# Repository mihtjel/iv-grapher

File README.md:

# iv-grapher
IV graphing electronics project. KiCAD design and Python (PyQT) based software.

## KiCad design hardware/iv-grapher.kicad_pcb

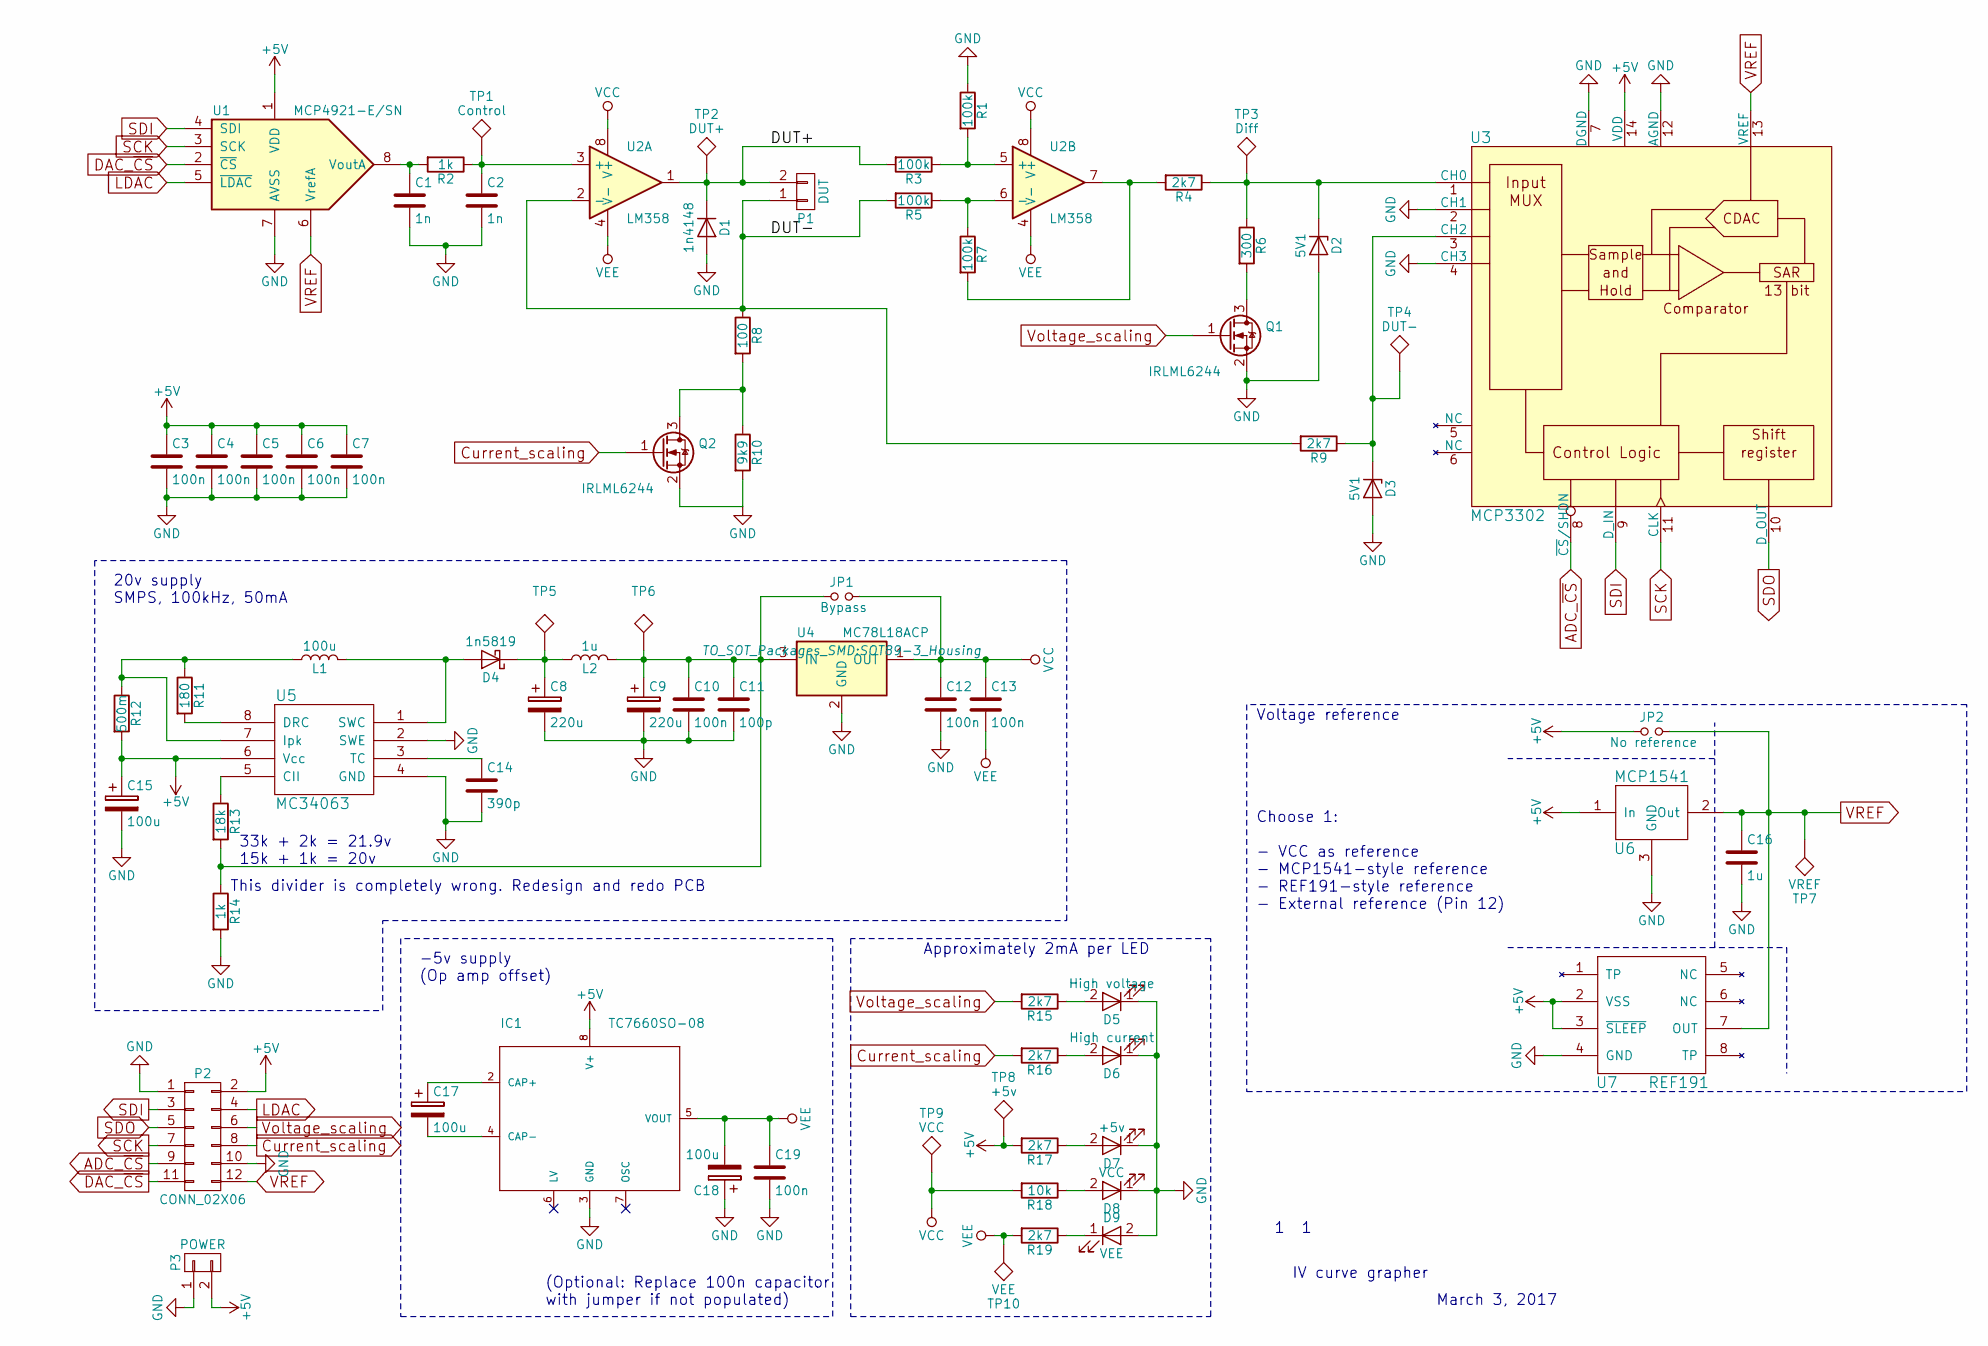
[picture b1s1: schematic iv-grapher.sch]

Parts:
C1, C2: 1n; C_0805
C3, C4, C5, C6, C7, C10, C12, C13, C19: 100n; C_0805
C8, C9: 220u; C_Radial_D8_L11.5_P3.5
C11: 100p; C_0805
C14: 390p; C_0805
C15, C17, C18: 100u; C_Radial_D6.3_L11.2_P2.5
C16: 1u; C_0805
D1: 1n4148; R_0805
D2, D3: 5V1; SOD-123
D4: 1n5819; SOD-123
D5: High voltage; R_0805
D6: High current; R_0805
D7: +5v; R_0805
D8: VCC; R_0805
D9: VEE; R_0805
IC1: TC7660SO-08; SOIC-8_3.9x4.9mm_Pitch1.27mm
JP1: Bypass; R_0805
JP2: No reference; R_0805
L1: 100u; Choke_SMD_6.3x6.3_H3
L2: 1u; R_0805
P1: DUT; DG306-5.0_2-pin
P2: CONN_02X06; IDC_Header_Straight_12pins
P3: POWER; Pin_Header_Straight_1x02
Q1, Q2: IRLML6244; SOT-23
R1, R3, R5, R7: 100k; R_0805
R2, R14: 1k; R_0805
R4, R9, R15, R16, R17, R19: 2k7; R_0805
R6: 300; R_0805
R8: 100; R_0805
R10: 9k9; R_0805
R11: 180; R_0805
R12: 500m; R_0805
R13: 18k; R_0805
R18: 10k; R_0805
TP1: Control; Measurement_Point_Round-SMD-Pad_Small
TP2: DUT+; Measurement_Point_Round-SMD-Pad_Small
TP3: Diff; Measurement_Point_Round-SMD-Pad_Small
TP4: DUT-; Measurement_Point_Round-SMD-Pad_Small
TP5: VCC pre filter; Measurement_Point_Round-SMD-Pad_Small
TP6: VCC post filter; Measurement_Point_Round-SMD-Pad_Small
TP7: VREF; Measurement_Point_Round-SMD-Pad_Small
TP8: +5v; Measurement_Point_Round-SMD-Pad_Small
TP9: VCC; Measurement_Point_Round-SMD-Pad_Small
TP10: VEE; Measurement_Point_Round-SMD-Pad_Small
U1: MCP4921-E/SN; SOIC-8_3.9x4.9mm_Pitch1.27mm
U2: LM358; SOIC-8_3.9x4.9mm_Pitch1.27mm
U3: MCP3302; SOIC-14_3.9x8.7mm_Pitch1.27mm
U4: MC78L18ACP; SOT89-3_Housing
U5: MC34063; SOIC-8_3.9x4.9mm_Pitch1.27mm
U6: MCP1541; SOT-23
U7: REF191; SOIC-8_3.9x4.9mm_Pitch1.27mm

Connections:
+5V: C3.1, C4.1, C5.1, C6.1, C7.1, C15.1, IC1.8 (V+), JP2.1, P2.2, P3.2, R12.2, R17.2, TP8.1, U1.1 (VDD), U3.14 (VDD), U5.6 (Vcc), U6.1 (In), U7.2 (VSS), U7.3 (~SLEEP)
/DUT+: D1.1 (K), P1.2, R3.2, TP2.1, U2.1
/DUT-: P1.1, R5.2, R8.1, R9.2, U2.2 (-)
ADC_~CS: P2.9, U3.8 (~CS~/SHDN)
Current_scaling: P2.8, Q2.1 (G), R16.2
DAC_~CS: P2.11, U1.2 (~CS~)
GND: C1.2, C2.2, C3.2, C4.2, C5.2, C6.2, C7.2, C8.2, C9.2, C10.2, C11.2, C12.2, C14.2, C15.2, C16.2, C18.1, C19.2, D1.2 (A), D2.2 (A), D3.2 (A), D5.1 (K), D6.1 (K), D7.1 (K), D8.1 (K), D9.2 (A), IC1.3 (GND), P2.1, P2.10, P3.1, Q1.2 (S), Q2.2 (S), R1.1, R10.2, R14.2, U1.7 (AVSS), U3.2 (CH1), U3.4 (CH3), U3.7 (DGND), U3.12 (AGND), U4.2 (GND), U5.2 (SWE), U5.4 (GND), U6.3 (GND), U7.4 (GND)
LDAC: P2.4, U1.5 (~LDAC~)
unnamed: C1.1, R2.2, U1.8 (VoutA)
unnamed: C2.1, R2.1, TP1.1, U2.3 (+)
unnamed: C8.1, D4.1 (K), L2.1, TP5.1
unnamed: C9.1, C10.1, C11.1, JP1.1, L2.2, R13.2, R14.1, TP6.1, U4.3 (IN)
unnamed: C14.1, U5.3 (TC)
unnamed: C17.1, IC1.2 (CAP+)
unnamed: C17.2, IC1.4 (CAP-)
unnamed: D2.1 (K), R4.1, R6.1, TP3.1, U3.1 (CH0)
unnamed: D3.1 (K), R9.1, TP4.1, U3.3 (CH2)
unnamed: D4.2 (A), L1.2, U5.1 (SWC)
unnamed: D5.2 (A), R15.1
unnamed: D6.2 (A), R16.1
unnamed: D7.2 (A), R17.1
unnamed: D8.2 (A), R18.1
unnamed: D9.1 (K), R19.1
unnamed: L1.1, R11.1, R12.1, U5.7 (Ipk)
unnamed: Q1.3 (D), R6.2
unnamed: Q2.3 (D), R8.2, R10.1
unnamed: R1.2, R3.1, U2.5 (+)
unnamed: R4.2, R7.2, U2.7
unnamed: R5.1, R7.1, U2.6 (-)
unnamed: R11.2, U5.8 (DRC)
unnamed: R13.1, U5.5 (CII)
SCK: P2.7, U1.3 (SCK), U3.11 (CLK)
SDI: P2.3, U1.4 (SDI), U3.9 (D_IN)
SDO: P2.5, U3.10 (D_OUT)
VCC: C12.1, C13.1, JP1.2, R18.2, TP9.1, U2.8 (V+), U4.1 (OUT)
VEE: C13.2, C18.2, C19.1, IC1.5 (VOUT), R19.2, TP10.1, U2.4 (V-)
VREF: C16.1, JP2.2, P2.12, TP7.1, U1.6 (VrefA), U3.13 (VREF), U6.2 (Out), U7.7 (OUT)
Voltage_scaling: P2.6, Q1.1 (G), R15.2

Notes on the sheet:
33k + 2k = 21.9v 15k + 1k = 20v
Approximately 2mA per LED
-5v supply (Op amp offset)
(Optional: Replace 100n capacitor with jumper if not populated)
Voltage reference
Choose 1: - VCC as reference - MCP1541-style reference - REF191-style reference - External reference (Pin 12)
20v supply SMPS, 100kHz, 50mA
IV curve grapher
March 3, 2017
This divider is completely wrong. Redesign and redo PCB

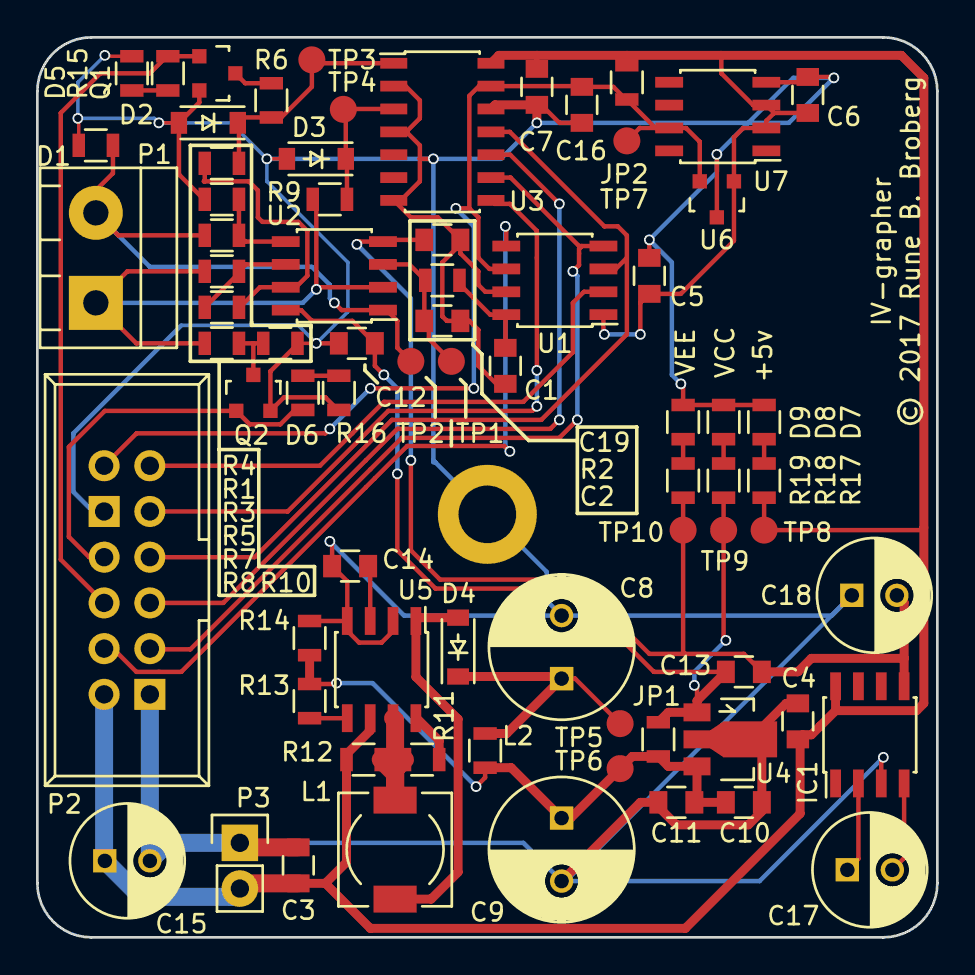
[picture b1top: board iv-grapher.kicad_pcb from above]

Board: 2 copper layers, 50.0 x 50.0 mm, 74 parts (0 on the bottom side), 38 nets.

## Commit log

2017-03-26 Structure, and existing Windows code
2017-03-26 Arduino control software
2017-03-26 - Additional IDE files (.idea) - Serial port handling
2017-03-26 Moved to fit Arduino software quirks
2017-03-26 Moved to fit Arduino quirks
2017-03-26 High voltage and high current options added.
2017-03-26 Layout improvements High/low voltage and current working Progress bar for sweeps
2017-03-28 Error dialog added. Locking for the serial port, to avoid simultaneous writes.
2017-03-28 Static calibration (+2mV from the ADC reading for the sample. Needs further testing.) Sweep bugfix
2017-03-30 Sweep averaging
2017-03-30 Lower serial speed for reliability
2017-03-31 Added KiCAD project
2017-04-01 - Multiple sweeps in one window, - Option of having a new sweep window, - Labels on sweeps, - Current correction from diff. amp. leakage, - Zero-current button, - Progress bar resets after a stopped 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
2017-04-01 - Min/max shading - Automatic ranging of sweep values - Minor fix of progress bar when starting/stopping sweeps
2017-04-06 Title of axis and plot for sweep plots.
2017-04-09 - Set static calibration to 0
2017-04-09 Start of design version 2

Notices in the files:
hardware/iv-grapher.kicad_pcb:
© 2017 Rune B. Broberg
